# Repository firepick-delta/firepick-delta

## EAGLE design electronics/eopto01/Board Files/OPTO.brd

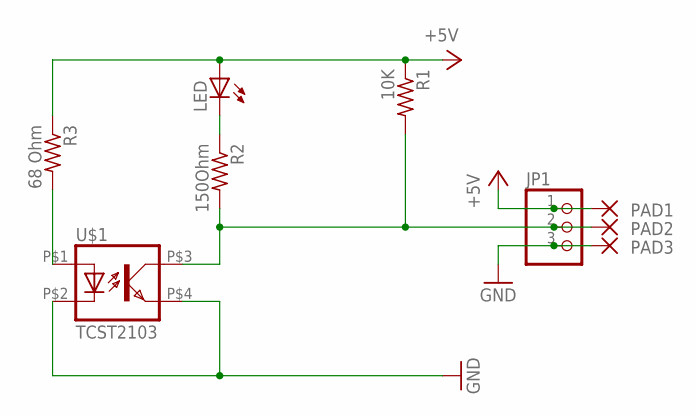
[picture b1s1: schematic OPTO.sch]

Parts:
JP1: PINHD-1X3CB; 1X03-CLEANBIG
LED: LEDCHIPLED_0805; CHIPLED_0805
PAD1, PAD2, PAD3: WIREPADSMD1,27-254; SMD1,27-2,54
R1: 10K; R0805
R2: 150Ohm; R0805
R3: 68 Ohm; R0805
U$1: TCST2103

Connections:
+5V: JP1.1, LED.A, PAD1.1, R1.1, R3.1
GND: JP1.3, PAD3.1, U$1.P$2 (C), U$1.P$4 (EMIT)
unnamed: LED.C, R2.1
unnamed: R3.2, U$1.P$1 (A)
unnamed: JP1.2, PAD2.1, R1.2, R2.2, U$1.P$3 (COL)

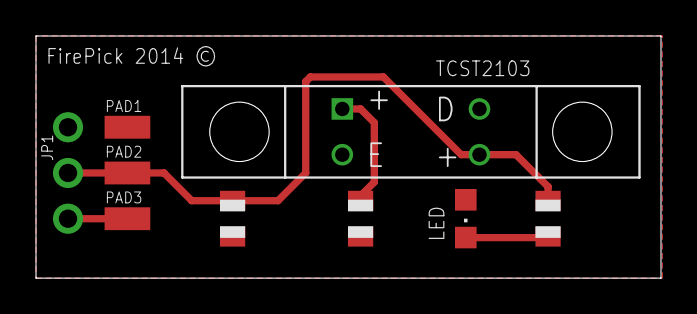
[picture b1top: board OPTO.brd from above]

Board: 4 copper layers, 34.7 x 13.5 mm, 9 parts (0 on the bottom side), 5 nets.
